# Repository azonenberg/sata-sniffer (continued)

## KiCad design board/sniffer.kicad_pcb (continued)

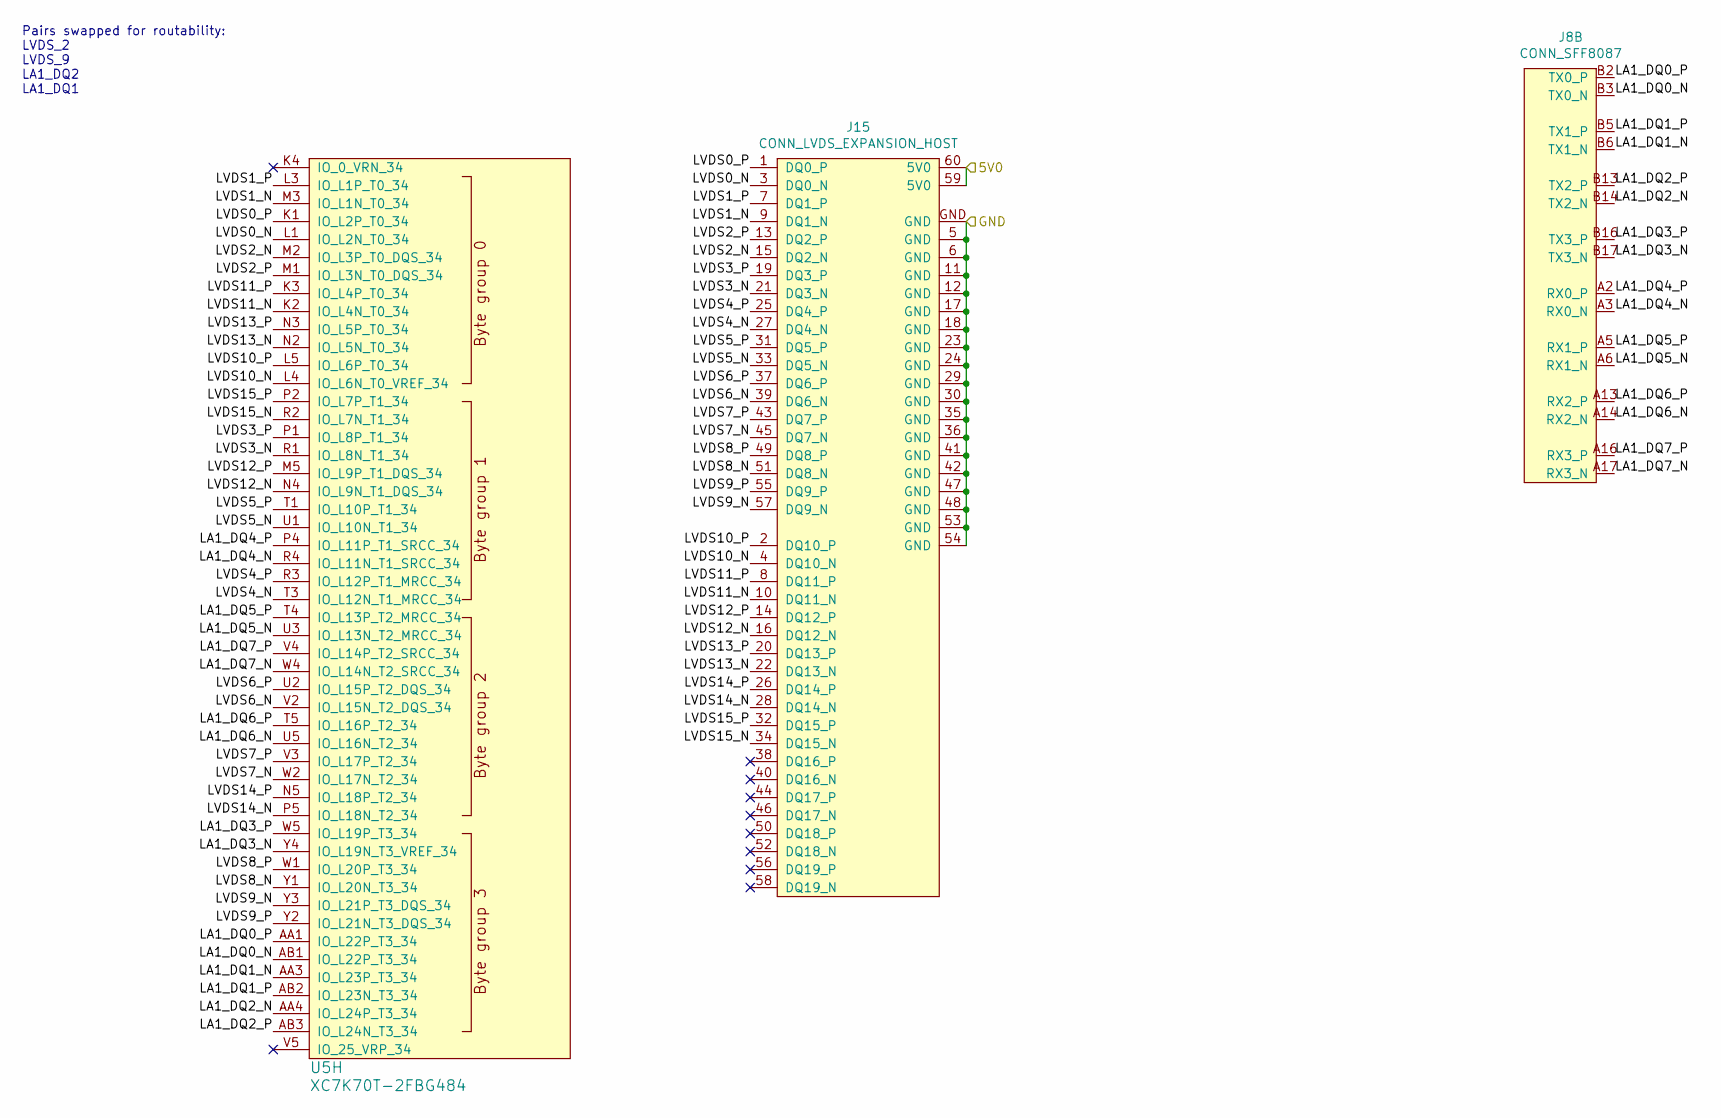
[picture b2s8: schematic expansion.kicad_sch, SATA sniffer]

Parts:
J8: CONN_SFF8087; CONN_SFF8087_MOLEX_75783-0140
J15: CONN_LVDS_EXPANSION_HOST; CONN_SAMTEC_QTH-030-01-L-D-A
U5: XC7K70T-2FBG484; BGA_484_22x22_FULLARRAY_1MM

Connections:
/5V0: J15.59 (5V0), J15.60 (5V0); also elsewhere on the board
/Expansion connector/LA1_DQ0_N: J8.B3 (TX0_N), U5.AB1 (IO_L22P_T3_34)
/Expansion connector/LA1_DQ0_P: J8.B2 (TX0_P), U5.AA1 (IO_L22P_T3_34)
/Expansion connector/LA1_DQ1_N: J8.B6 (TX1_N), U5.AA3 (IO_L23P_T3_34)
/Expansion connector/LA1_DQ1_P: J8.B5 (TX1_P), U5.AB2 (IO_L23N_T3_34)
/Expansion connector/LA1_DQ2_N: J8.B14 (TX2_N), U5.AA4 (IO_L24P_T3_34)
/Expansion connector/LA1_DQ2_P: J8.B13 (TX2_P), U5.AB3 (IO_L24N_T3_34)
/Expansion connector/LA1_DQ3_N: J8.B17 (TX3_N), U5.Y4 (IO_L19N_T3_VREF_34)
/Expansion connector/LA1_DQ3_P: J8.B16 (TX3_P), U5.W5 (IO_L19P_T3_34)
/Expansion connector/LA1_DQ4_N: J8.A3 (RX0_N), U5.R4 (IO_L11N_T1_SRCC_34)
/Expansion connector/LA1_DQ4_P: J8.A2 (RX0_P), U5.P4 (IO_L11P_T1_SRCC_34)
/Expansion connector/LA1_DQ5_N: J8.A6 (RX1_N), U5.U3 (IO_L13N_T2_MRCC_34)
/Expansion connector/LA1_DQ5_P: J8.A5 (RX1_P), U5.T4 (IO_L13P_T2_MRCC_34)
/Expansion connector/LA1_DQ6_N: J8.A14 (RX2_N), U5.U5 (IO_L16N_T2_34)
/Expansion connector/LA1_DQ6_P: J8.A13 (RX2_P), U5.T5 (IO_L16P_T2_34)
/Expansion connector/LA1_DQ7_N: J8.A17 (RX3_N), U5.W4 (IO_L14N_T2_SRCC_34)
/Expansion connector/LA1_DQ7_P: J8.A16 (RX3_P), U5.V4 (IO_L14P_T2_SRCC_34)
/Expansion connector/LVDS0_N: J15.3 (DQ0_N), U5.L1 (IO_L2N_T0_34)
/Expansion connector/LVDS0_P: J15.1 (DQ0_P), U5.K1 (IO_L2P_T0_34)
/Expansion connector/LVDS1_N: J15.9 (DQ1_N), U5.M3 (IO_L1N_T0_34)
/Expansion connector/LVDS1_P: J15.7 (DQ1_P), U5.L3 (IO_L1P_T0_34)
/Expansion connector/LVDS2_N: J15.15 (DQ2_N), U5.M2 (IO_L3P_T0_DQS_34)
/Expansion connector/LVDS2_P: J15.13 (DQ2_P), U5.M1 (IO_L3N_T0_DQS_34)
/Expansion connector/LVDS3_N: J15.21 (DQ3_N), U5.R1 (IO_L8N_T1_34)
/Expansion connector/LVDS3_P: J15.19 (DQ3_P), U5.P1 (IO_L8P_T1_34)
/Expansion connector/LVDS4_N: J15.27 (DQ4_N), U5.T3 (IO_L12N_T1_MRCC_34)
/Expansion connector/LVDS4_P: J15.25 (DQ4_P), U5.R3 (IO_L12P_T1_MRCC_34)
/Expansion connector/LVDS5_N: J15.33 (DQ5_N), U5.U1 (IO_L10N_T1_34)
/Expansion connector/LVDS5_P: J15.31 (DQ5_P), U5.T1 (IO_L10P_T1_34)
/Expansion connector/LVDS6_N: J15.39 (DQ6_N), U5.V2 (IO_L15N_T2_DQS_34)
/Expansion connector/LVDS6_P: J15.37 (DQ6_P), U5.U2 (IO_L15P_T2_DQS_34)
/Expansion connector/LVDS7_N: J15.45 (DQ7_N), U5.W2 (IO_L17N_T2_34)
/Expansion connector/LVDS7_P: J15.43 (DQ7_P), U5.V3 (IO_L17P_T2_34)
/Expansion connector/LVDS8_N: J15.51 (DQ8_N), U5.Y1 (IO_L20N_T3_34)
/Expansion connector/LVDS8_P: J15.49 (DQ8_P), U5.W1 (IO_L20P_T3_34)
/Expansion connector/LVDS9_N: J15.57 (DQ9_N), U5.Y3 (IO_L21P_T3_DQS_34)
/Expansion connector/LVDS9_P: J15.55 (DQ9_P), U5.Y2 (IO_L21N_T3_DQS_34)
/Expansion connector/LVDS10_N: J15.4 (DQ10_N), U5.L4 (IO_L6N_T0_VREF_34)
/Expansion connector/LVDS10_P: J15.2 (DQ10_P), U5.L5 (IO_L6P_T0_34)
/Expansion connector/LVDS11_N: J15.10 (DQ11_N), U5.K2 (IO_L4N_T0_34)
/Expansion connector/LVDS11_P: J15.8 (DQ11_P), U5.K3 (IO_L4P_T0_34)
/Expansion connector/LVDS12_N: J15.16 (DQ12_N), U5.N4 (IO_L9N_T1_DQS_34)
/Expansion connector/LVDS12_P: J15.14 (DQ12_P), U5.M5 (IO_L9P_T1_DQS_34)
/Expansion connector/LVDS13_N: J15.22 (DQ13_N), U5.N2 (IO_L5N_T0_34)
/Expansion connector/LVDS13_P: J15.20 (DQ13_P), U5.N3 (IO_L5P_T0_34)
/Expansion connector/LVDS14_N: J15.28 (DQ14_N), U5.P5 (IO_L18N_T2_34)
/Expansion connector/LVDS14_P: J15.26 (DQ14_P), U5.N5 (IO_L18P_T2_34)
/Expansion connector/LVDS15_N: J15.34 (DQ15_N), U5.R2 (IO_L7N_T1_34)
/Expansion connector/LVDS15_P: J15.32 (DQ15_P), U5.P2 (IO_L7P_T1_34)

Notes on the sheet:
Pairs swapped for routability: LVDS_2 LVDS_9 LA1_DQ2 LA1_DQ1

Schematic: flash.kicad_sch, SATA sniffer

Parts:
C72, C73, C74: 4.7 uF; EIA_0603_CAP_NOSILK
C75, C76, C77, C78, C79, C80, C81, C82, C83: 0.47 uF; EIA_0402_CAP_NOSILK
R26: 33; EIA_0402_RES_NOSILK
R27, R69, R70: 10K; EIA_0402_RES_NOSILK
U11, U12, U13, U14: 74AVCH1T45; DFN_6_0.5MM_1.45x1.00MM
U15: W25Q128JV; DFN_8_1.27MM_6x5MM

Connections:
/1V8: C73.1, C76.1, U14.1 (VCCA), U14.5 (DIR); also elsewhere on the board
/1V35: C74.1, C77.1, C79.1, C81.1, U11.1 (VCCA), U11.5 (DIR), U12.1 (VCCA), U13.1 (VCCA), U13.5 (DIR); also elsewhere on the board
/3V3: C72.1, C75.1, C78.1, C80.1, C82.1, C83.1, R27.2, R69.2, R70.1, U11.6 (VCCB), U12.6 (VCCB), U13.6 (VCCB), U14.6 (VCCB), U15.8 (VCC); also elsewhere on the board
/Boot flash/FLASH_CS: U11.3 (A); also elsewhere on the board
/Boot flash/FLASH_CS_SHIFT: R27.1, U11.4 (B), U15.1 (CS#)
/Boot flash/FLASH_SCK: U14.3 (A); also elsewhere on the board
/Boot flash/FLASH_SCK_SHIFT: U14.4 (B), U15.6 (CLK)
/Boot flash/FLASH_SI: U13.3 (A); also elsewhere on the board
/Boot flash/FLASH_SI_SHIFT: U13.4 (B), U15.5 (DI/IO0)
/Boot flash/FLASH_SO: R26.2; also elsewhere on the board
/Boot flash/FLASH_SO_SHIFT: U12.4 (B), U15.2 (DO/IO1)
unnamed: R26.1, U12.3 (A)
unnamed: R69.1, U15.3 (WP#/IO2)
unnamed: R70.2, U15.7 (HOLD#/IO3)

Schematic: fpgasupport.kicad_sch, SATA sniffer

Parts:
D1: GREEN; EIA_0402_LED
J4: XILINX_JTAG; XILINX_JTAG_PTH_MOLEX_0878311420
Q1: SSM6N58NU; DFN_6_0.65MM_2x2MM_GDS
R28, R29: 4.7K; EIA_0402_RES_NOSILK
R30, R31: 33; EIA_0402_RES_NOSILK
R32: 470; EIA_0402_RES_NOSILK
TP1, TP2: TESTPOINT; TESTPOINT_SMT_0.5MM
U5: XC7K70T-2FBG484; BGA_484_22x22_FULLARRAY_1MM

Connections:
/1V8: J4.2 (Vccaux), R28.2, R29.2, U5.H7 (M0); also elsewhere on the board
/3V3: R32.1; also elsewhere on the board
/Boot flash/FLASH_SCK: R31.2; also elsewhere on the board
/FPGA support/FPGA_DONE: Q1.G1 (G), TP1.1, U5.P6 (DONE)
/FPGA support/FPGA_INIT_B: R28.1, TP2.1, U5.L7 (INIT_B)
/FPGA support/FPGA_RST_N: R29.1, U5.M6 (PROG_B)
/FPGA support/JTAG_TCK: J4.6 (TCK), U5.K7 (TCK)
/FPGA support/JTAG_TDI: J4.10 (TDI_OUT), U5.K6 (TDI)
/FPGA support/JTAG_TDO: J4.8 (TDO_IN), R30.2
/FPGA support/JTAG_TMS: J4.4 (TMS), U5.L6 (TMS)
unnamed: D1.1 (K), Q1.D1 (D)
unnamed: D1.2 (A), R32.2
unnamed: R30.1, U5.J6 (TDO)
unnamed: R31.1, U5.G7 (CCLK)

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
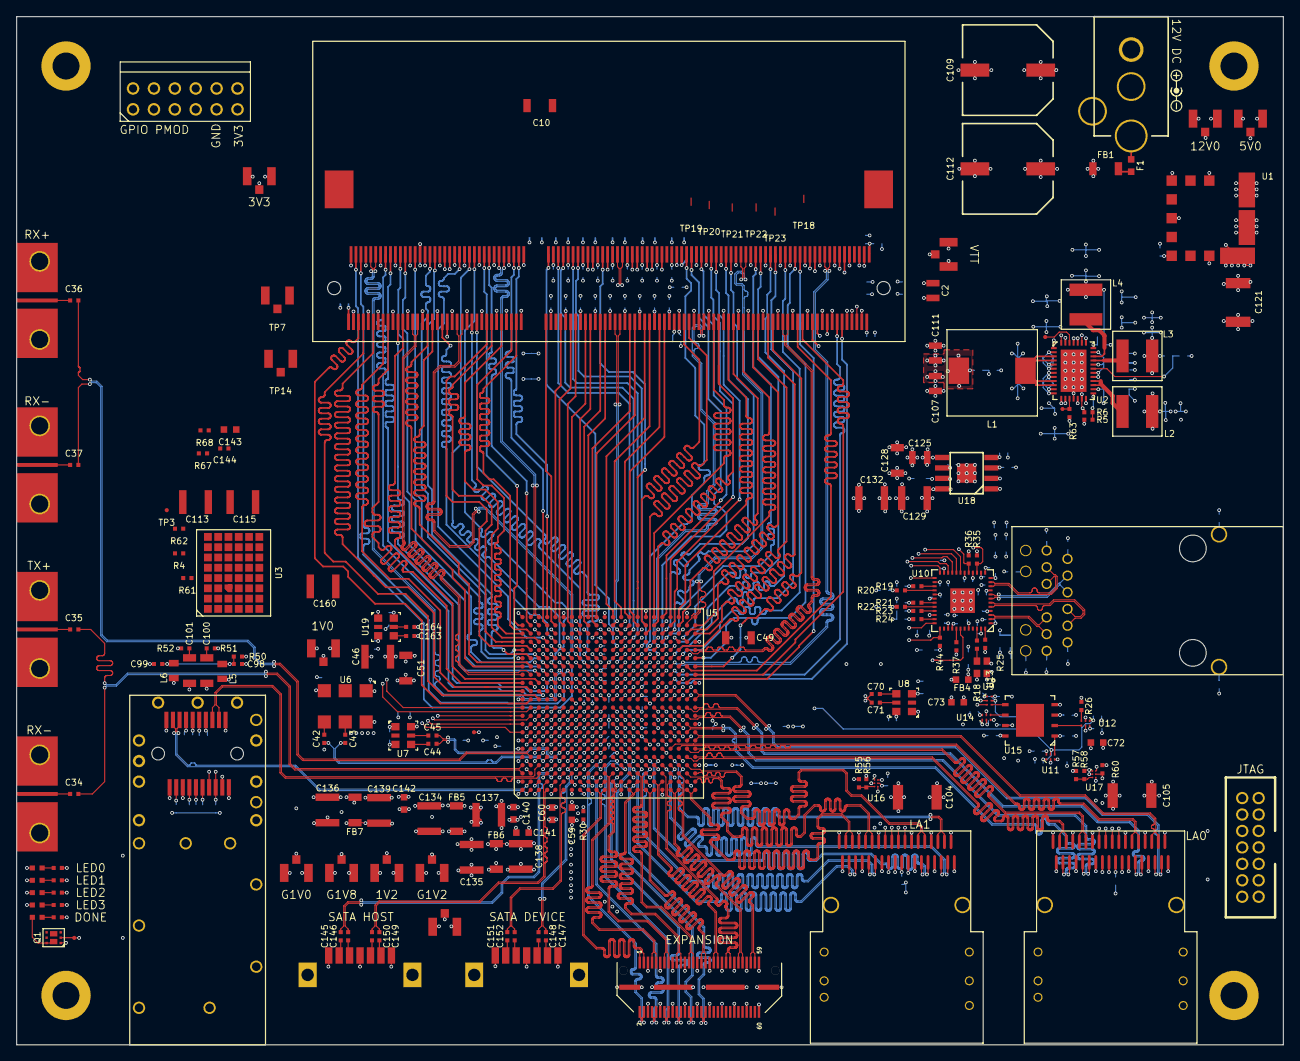
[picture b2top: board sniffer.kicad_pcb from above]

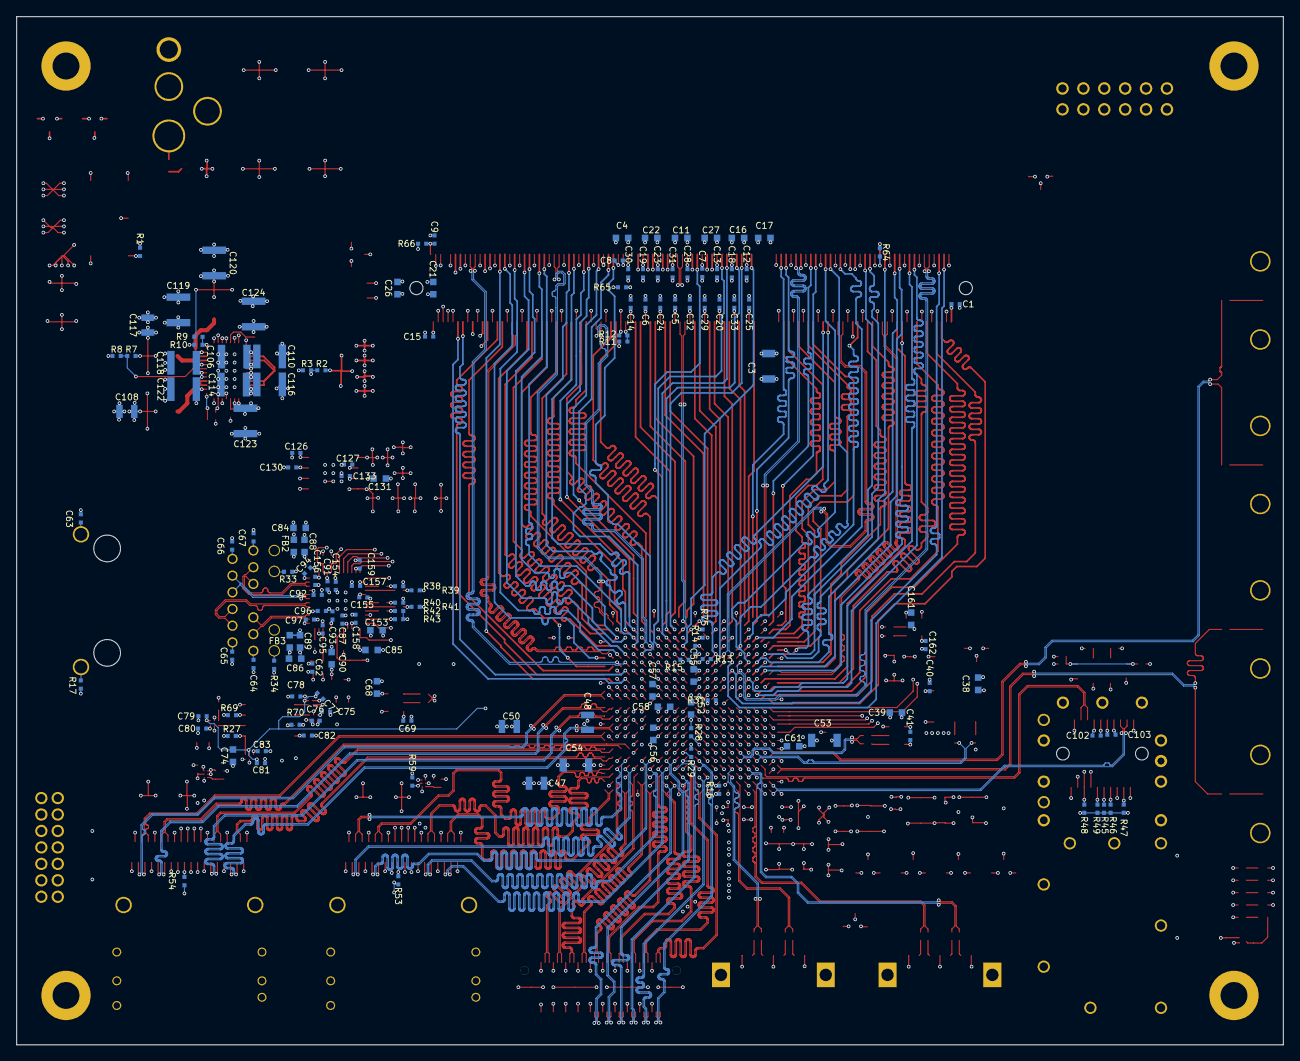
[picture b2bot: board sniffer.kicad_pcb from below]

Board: 8 copper layers, 154.0 x 125.0 mm, 320 parts (148 on the bottom side), 381 nets.

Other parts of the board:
C143: 4.7 uF; EIA_0603_CAP_NOSILK
C144: 0.47 uF; EIA_0402_CAP_NOSILK
R67, R68: 1K; EIA_0402_RES_NOSILK

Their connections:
/1V35: R67.1; also elsewhere on the board

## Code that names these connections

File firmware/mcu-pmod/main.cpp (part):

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{
	//Initialize the UART for local console: 115.2 Kbps using PA12 for UART4 transmit and PA11 for UART2 receive
	//TODO: nice interface for enabling UART interrupts
	GPIOPin uart_tx(&GPIOA, 12, GPIOPin::MODE_PERIPHERAL, GPIOPin::SLEW_SLOW, 6);
	GPIOPin uart_rx(&GPIOA, 11, GPIOPin::MODE_PERIPHERAL, GPIOPin::SLEW_SLOW, 6);

	//Default after reset is for UART4 to be clocked by PCLK1 (APB1 clock) which is 68.75 MHz
	//So we need a divisor of 596.78
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{
	g_log("Initializing I2C interface\n");

	static GPIOPin i2c_scl(&GPIOD, 12, GPIOPin::MODE_PERIPHERAL, GPIOPin::SLEW_SLOW, 4, true);
	static GPIOPin i2c_sda(&GPIOD, 13, GPIOPin::MODE_PERIPHERAL, GPIOPin::SLEW_SLOW, 4, true);

	//Default kernel clock for I2C4 is pclk4 (68.75 MHz for our current config)
	//Prescale by 16 to get 4.29 MHz
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		OctoSPIManager::PORT_1);	//Clock from OCTOSPI1

	//Configure the I/O pins
	static GPIOPin qspi_cs_n(&GPIOE, 11, GPIOPin::MODE_PERIPHERAL, GPIOPin::SLEW_VERYFAST, 11);
	static GPIOPin qspi_sck(&GPIOB, 2, GPIOPin::MODE_PERIPHERAL, GPIOPin::SLEW_VERYFAST, 9);
	static GPIOPin qspi_dq0(&GPIOA, 2, GPIOPin::MODE_PERIPHERAL, GPIOPin::SLEW_VERYFAST, 6);
	static GPIOPin qspi_dq1(&GPIOB, 0, GPIOPin::MODE_PERIPHERAL, GPIOPin::SLEW_VERYFAST, 4);
	static GPIOPin qspi_dq2(&GPIOC, 2, GPIOPin::MODE_PERIPHERAL, GPIOPin::SLEW_VERYFAST, 9);
	static GPIOPin qspi_dq3(&GPIOA, 1, GPIOPin::MODE_PERIPHERAL, GPIOPin::SLEW_VERYFAST, 9);

	//Clock divider value
	//Default is for AHB3 bus clock to be used as kernel clock (275 MHz for us)
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
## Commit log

2021-11-10 Continued work on schematic. DDR power decoupling, FPGA decoupling, lots more block diagram
2021-11-11 Added flash and FPGA support pages, initial DDR pinout, started work on 1G PHY
2021-11-12 More work on schematic including 3.3V I/O, power supply, SERDES lines, etc
2021-11-12 Updated date
2021-11-13 Finished initial schematic, ready for design review
2021-11-17 Finished initial schematic review
2021-11-18 Picked footprints for all components. No actual stackup or layout work done yet.
2021-11-19 Updating with progress from tonight
2021-11-29 Added lots of simulations for vias and impedance calculations
2021-11-30 Began actual layout!
2021-11-30 Redid all of the simulations with new stackup based on conversations with fab
2021-11-30 Continued initial work on layout. BGA fanout and southwest area
2021-12-01 Continued routing for tonight. Bunch of low speed stuff in south area of board.
2021-12-02 Finished routing of south area of board including low speed SFP+ and LA connections. Started work on Ethernet.
2021-12-03 Finished routing almost everything except DDR.
2021-12-04 Added antikernel-ipcores submodule
2021-12-04 Initial RTL skeleton project
2021-12-04 Initial skeleton of RAM matching spreadsheet
2021-12-04 Initial Vivado project
2021-12-07 Preliminary layout of DQ byte groups 3:0 on DDR3. Not length matched.
2021-12-07 Finished initial routing of DDR C/A bus
2021-12-08 Fully routed DDR. Length matched first three DQ groups.
2021-12-11 Continued work on layout. Finished length matchnig all DQ byte groups. Still have to do C/A bus.
2021-12-11 Matched about 2/3 of the C/A bus
2021-12-14 Finished initial layout. Added power planes and some initial test points
2022-01-05 Added a ton of SI simulations
2022-01-31 Lots of updates to SATA area simulations
2022-01-31 Removed a bunch of simulations that are way out of date
2022-01-31 Removed even more unused sims
2022-02-01 Continued work on layout. Added via fences, stitching vias, general silkscreen tweaks, etc
2022-02-13 Added simulations for the SFP+
2022-02-13 Added lots of stitching vias and ground cutouts
2022-02-16 Deleted a bunch of simulations that are no longer current, updated some existing sims
2022-02-16 Added stitching vias to SFP+ GTX line layer changes
2022-02-19 Added power rail test point simulation
2022-02-19 Hopefully-final layout after implementation of design review changes
2022-02-19 One (hopefully) final change: Added position marker for UL mark / date code
2022-02-19 Actually export F.Fab layer
2022-02-19 Final edits to fab notes file
2022-02-19 Updated fab notes with correct file names, replaced tabs with spaces
2022-02-19 Removed solder paste from SMA compression fit ground pads. Moved "12V DC" text to not overlap bare PCB edge
2022-02-19 Moved U1 refdes to not overlap bare PCB edge
2022-02-26 Updated FPGA design
2022-02-26 Removed old DDR DQ simulations, will recreate with new stackup
2022-02-27 Re-ran trace simulations with updated stackup
2022-02-28 v0.1c layout with new stackup
2022-03-04 Updated EM simulations with new stackup
2022-03-04 Re-ran DRC one last time. Updated export settings so silkscreen is removed from soldermask apertures
2022-03-04 Updated fab notes for v0.1c rev number
2022-04-13 Updated ignore properties for board
2022-04-13 Continued initial work on LA capture
2022-04-14 Initial work on RLE compression engine
2022-04-14 Fixed lane inversion
2022-04-15 Initial SERDES bringup
2022-04-15 Switched from MMCM to PLL for 400 MHz clock domain to free up a MMCM for other uses that actually need the extra features
2022-04-16 board: Convert project to KiCad 6
    - Fix missing symbols because of missing library cache file in
    git.
    - Fix unconnected symbols caused by auto converting.
    - Delete KiCad 5 files.
2022-04-17 Lots of progress bringing up IP stack subsystem. Failing timing in TX MAC CRC calculation, probably need to pipeline it like we did with RX.
2022-04-18 Updated submodules
2022-04-18 Added floorplan constraints to LA sampling block
2022-04-19 RPM work on LogicPodSampling to improve timing consistency. Added RX_LOS to SFPInterface
2022-04-21 Updated floorplan constraints to leave space up top for SATA. Moved logic pod stuff to separate module.
2022-04-23 Continued logic analyzer pod work. Now have arbitration between LA channels up to a single memory bus per pod. Doesn't write to DDR yet.
2022-04-24 Continued work on DRAM arbitration path for LA
2022-04-24 Added MemorySubsystem
2022-04-25 Continued work on memory arbitration
2022-04-26 Progress on memory arbitration
2022-04-27 Major rework of memory arbiter subsystem
2022-04-27 LogicPodDatapath: can now do writes to fifo back to back
2022-04-28 Write side of memory arbiter seems to be working OK up to but not including last FIFO. Read side of last FIFO not well tested yet.
2022-04-29 Continued work on MemoryArbiter. Everything appears to be working in write-only mode. But no read capability, and not tested well.
2022-04-29 Fixed output data to RAM being set incorrectly
2022-04-30 Added performance counters for various DRAM speed metrics. Changed MIG from 4 to 8 bank machines.
2022-04-30 LA: refactored LogicPodArbiter out into its own module for better floorplanning
2022-04-30 Minor tweaks to floorplanning constraints for capture logic. Fixed missing BUFIO. Tweaked memory arbitration.
2022-05-08 Initial work on triggering
2022-05-08 RAM performance test spreadsheet
2022-05-09 Continued work on trigger capture/flush logic
2022-05-17 Initial work on mcu-pmod board
2022-05-17 Final rev of mcu-pmod
2022-06-01 v0.2 of mcu-pmod with correct STM32 footprint
2022-06-10 Fixed pin swap
2022-06-11 Added a bunch of submodules for firmware dev
2022-06-12 Initial skeleton firmware for mcu-pmod. Just turns on some LEDs, nothing too exciting.
2022-06-12 Initial work on logic analyzer readback
2022-06-12 Updated ILAs
2022-06-12 Added 50 MHz clock output on pmod connector
2022-06-12 Updated stm32-cpp
2022-06-13 Fixed TX/RX swap in schematic
2022-06-13 Initial firmware now supports basic UART logging and device info
2022-06-13 Brought up initial CLI and KVS
2022-07-18 Read MAC address and serial number from I2C EEPROM
2022-07-26 Continued work on QSPI integration
2022-07-27 Can now configure IP address, subnet mask, etc via MCU and push to FPGA via QSPI
2022-07-28 Various area tweaks to buffer sizes in Ethernet subsystem
